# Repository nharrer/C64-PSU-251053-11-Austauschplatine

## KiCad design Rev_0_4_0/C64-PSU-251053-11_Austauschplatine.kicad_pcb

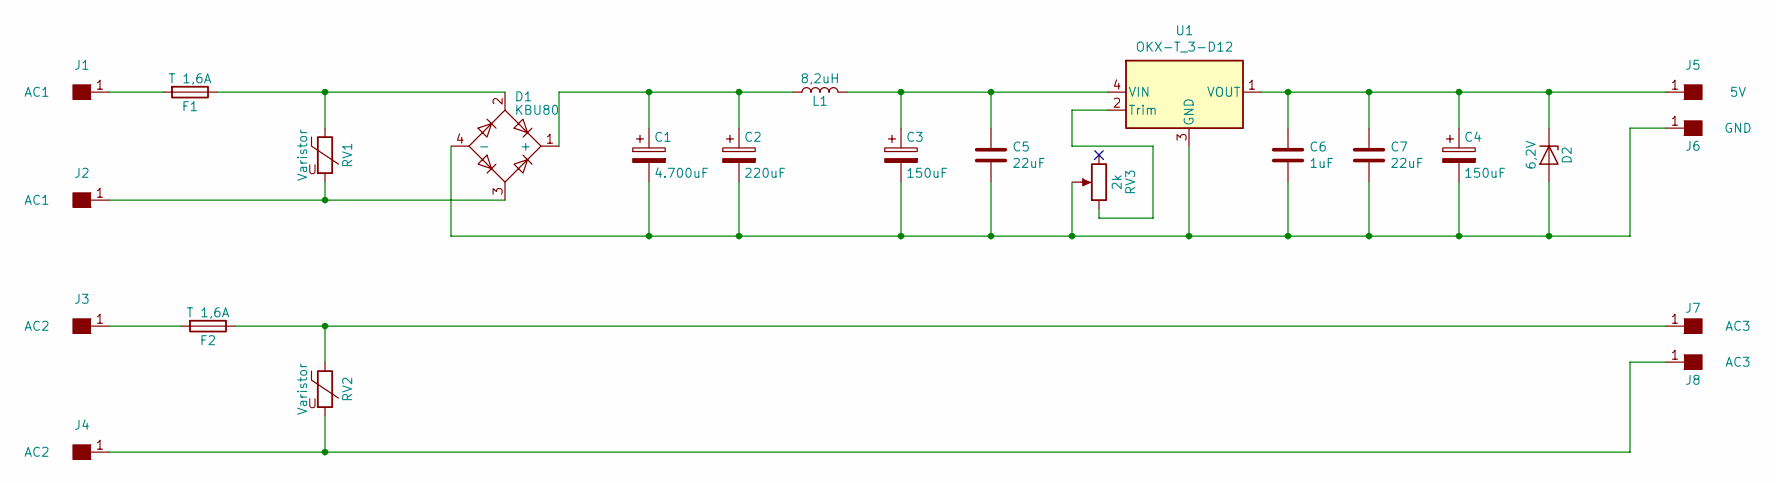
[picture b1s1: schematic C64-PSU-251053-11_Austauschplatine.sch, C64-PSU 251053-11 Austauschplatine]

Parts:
C1: 4.700uF; CP_Radial_D18.0mm_P7.50mm
C2: 220uF; CP_Radial_D8.0mm_P3.50mm
C3, C4: 150uF; CP_Radial_D8.0mm_P3.50mm
C5, C7: 22uF; C_1210_HandSoldering
C6: 1uF; C_1210_HandSoldering
D1: KBU80; Diode_Bridge_Vishay_KBU
D2: 6,2V; D_DO-41_SOD81_P5.08mm_Vertical_KathodeUp
F1, F2: T 1,6A; Fuseholder5x20_horiz_open_inline_Type-I
J1, J2: AC1; Measurement_Point_Square-TH_Big
J3, J4: AC2; Measurement_Point_Square-TH_Big
J5: 5V; Measurement_Point_Square-TH_Big
J6: GND; Measurement_Point_Square-TH_Big
J7, J8: AC3; Measurement_Point_Square-TH_Big
L1: 8,2uH; L_Radial_D9.5mm_P5.00mm_Fastron_07HVP
RV1, RV2: Varistor; RV_Disc_D12_W4.5_P7.5
RV3: 2k; Potentiometer_Trimmer_Vishay_43
U1: OKX-T_3-D12; Murata_OKX-T3-D12

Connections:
unnamed: C1.1, C2.1, D1.1 (+), L1.1
unnamed: C1.2, C2.2, C3.2, C4.2, C5.2, C6.2, C7.2, D1.4 (-), D2.2 (A), J6.1, RV3.2, U1.3 (GND)
unnamed: C3.1, C5.1, L1.2, U1.4 (VIN)
unnamed: C4.1, C6.1, C7.1, D2.1 (K), J5.1, U1.1 (VOUT)
unnamed: D1.2, F1.1, RV1.1
unnamed: D1.3, J2.1, RV1.2
unnamed: F1.2, J1.1
unnamed: F2.1, J7.1, RV2.1
unnamed: F2.2, J3.1
unnamed: J4.1, J8.1, RV2.2
unnamed: RV3.1, U1.2 (Trim)

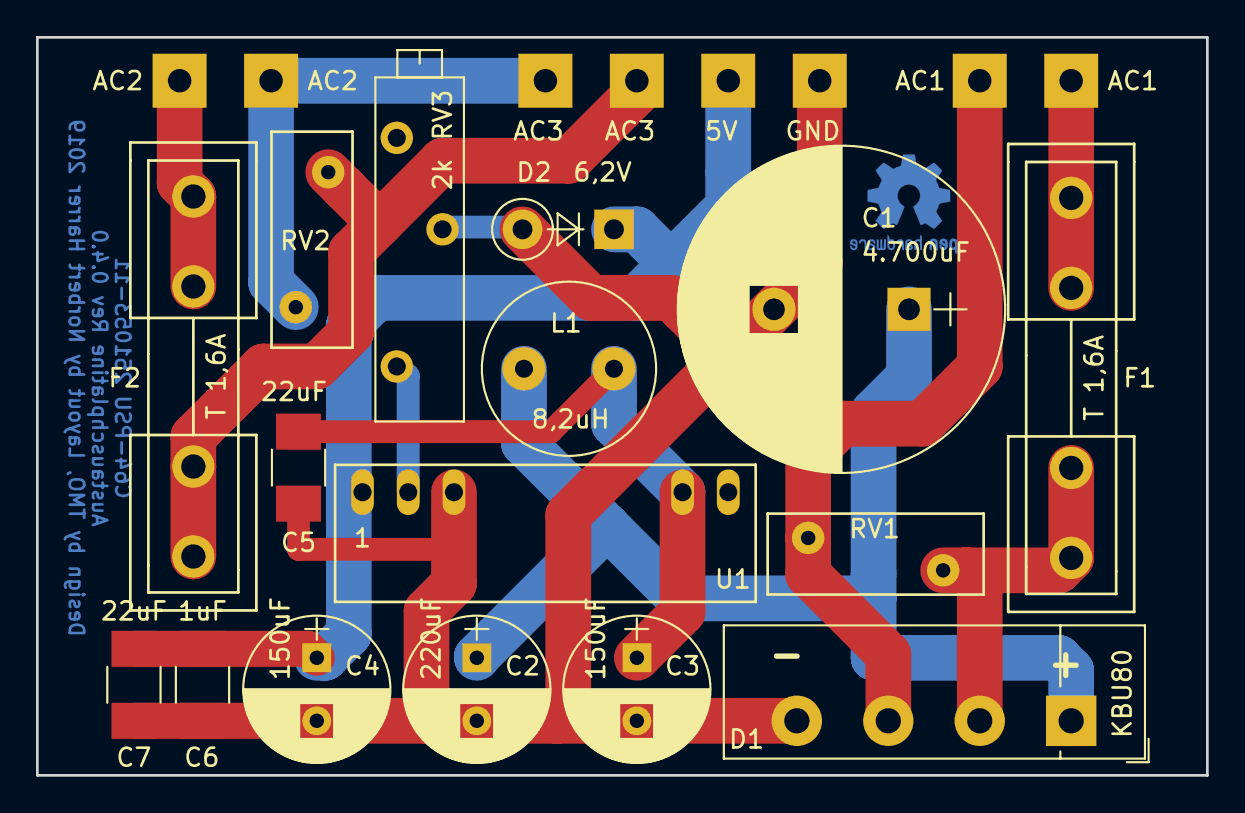
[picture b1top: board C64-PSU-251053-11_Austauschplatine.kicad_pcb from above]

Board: 2 copper layers, 65.0 x 41.0 mm, 24 parts (0 on the bottom side), 11 nets.

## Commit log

2019-10-16 Rev 4 mit Murata OKX-T/3-D12N-C
2020-08-05 Fehlende .lib Dateien
2020-08-05 Abmessungen des Boards hinzugefügt
2020-08-05 Gerber Files für Produktion
